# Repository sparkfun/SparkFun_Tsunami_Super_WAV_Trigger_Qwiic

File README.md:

SparkFun Tsunami Super WAV Trigger (Qwiic)
========================================

<table class="table table-hover table-striped table-bordered">
  <tr align="center">
   <td></td>
   <td></td>
  </tr>
  <tr align="center">
   <td><i>SparkFun Tsunami Super WAV Trigger (Qwiic)<br /> - 32 Voices <br />[ <a href="https://www.sparkfun.com/products/18159">WIG-18159</a> ]</i></td>
   <td><i>SparkFun Tsunami Super WAV Trigger (Qwiic)<br /> - 25 Voices <br />[ <a href="https://www.sparkfun.com/products/20636">WIG-20636</a> ]</i></td>
  </tr>
</table>

Tsunami is a polyphonic Wav file player with 4 stereo (or 8 mono) outputs.  Wav files can be triggered using the 16 onboard contacts, via MIDI, serial connection or Qwiic to a PC or other microcontroller.

Repository Contents
-------------------

* **/Documentation** - Data sheets, additional product information
* **/Hardware** - Eagle design files (.brd, .sch)
* **/Production** - Production panel files (.brd)
* **/Example_WAV_files/MONO** - example WAV Files for use with _mono_ firmware and the [Qwiic Arduino Library Examples](https://github.com/sparkfun/SparkFun_Tsunami_Qwiic_Arduino_Library).
* **/Example_WAV_files/STEREO** - example WAV Files for use with _stereo_ firmware

Documentation
--------------
* **[Hookup Guide](https://learn.sparkfun.com/tutorials/tsunami-super-wav-trigger-hookup-guide)** - Basic hookup guide for Tsunami Qwiic.
* **[Official User Guide](https://cdn.sparkfun.com/assets/e/9/9/8/e/Tsunami_UserGuide_20230114.pdf)** - More detailed user guide, written by Robertsonics.
* **[Official Downloads Page](http://robertsonics.com/downloads/)** - Download supporting files, including firmware updates and the configuration utility.
* **[SparkFun Tsunami Qwiic Arduino Library](https://github.com/sparkfun/SparkFun_Tsunami_Qwiic_Arduino_Library)** - Arduino Library for I2C control via Qwiic cable.
* **[Tsunami Arduino Serial Library](https://github.com/robertsonics/Tsunami-Arduino-Serial-Library)** - Arduino Library for Serial interface control via RX/TX.
* **[SparkFun Fritzing repo](https://github.com/sparkfun/Fritzing_Parts/blob/main/products/13810_Tsunami_Super_WAV_Trigger.fzpz)** - Fritzing diagrams for SparkFun products.
* **[SparkFun 3D Model repo](https://github.com/sparkfun/3D_Models)** - 3D models of SparkFun products.

Product Versions
----------------
* [WIG-20636](https://www.sparkfun.com/products/20636) - v21 with ATSAMS70N19, 25 Voices, and Qwiic supported! 
* [WIG-18159](https://www.sparkfun.com/products/18159) - v21 with ATSAMS70N20, 32 Voices, and Qwiic supported! 
* [WIG-13810](https://www.sparkfun.com/products/13810) - v11 First hardware revision (non-qwiic)

Version History
---------------
* [v21 Production Release](https://github.com/sparkfun/SparkFun_Tsunami_Super_WAV_Trigger_Qwiic/commit/4bed2473d8b69c6fbc46fcfe248d6b1637192635) - V21 hardware revision. There are different versions of this board that use the same PCB. To distinguish the two, check out the IC: ATSAMS70N20 for 32 voices and ATSAMS70N19 for 25 voices.
* [v11 Initial production Release](https://github.com/sparkfun/tsunami/commit/f42b14d72773535e83374cde73f2ca3f25164abb) - V11 hardware revision.

License Information
-------------------

The hardware design of Tsunami is _**open source**_!

Please review the LICENSE.md file for license information.

If you have any questions or concerns on licensing, please contact techsupport@sparkfun.com.

Distributed as-is; no warranty is given.

- Your friends at SparkFun.

Authors
----

Jamie Robertson @ Robertsonics, 
Pete Lewis @ SparkFun Electronics, 
Byron Jacquot @ SparkFun Electronics

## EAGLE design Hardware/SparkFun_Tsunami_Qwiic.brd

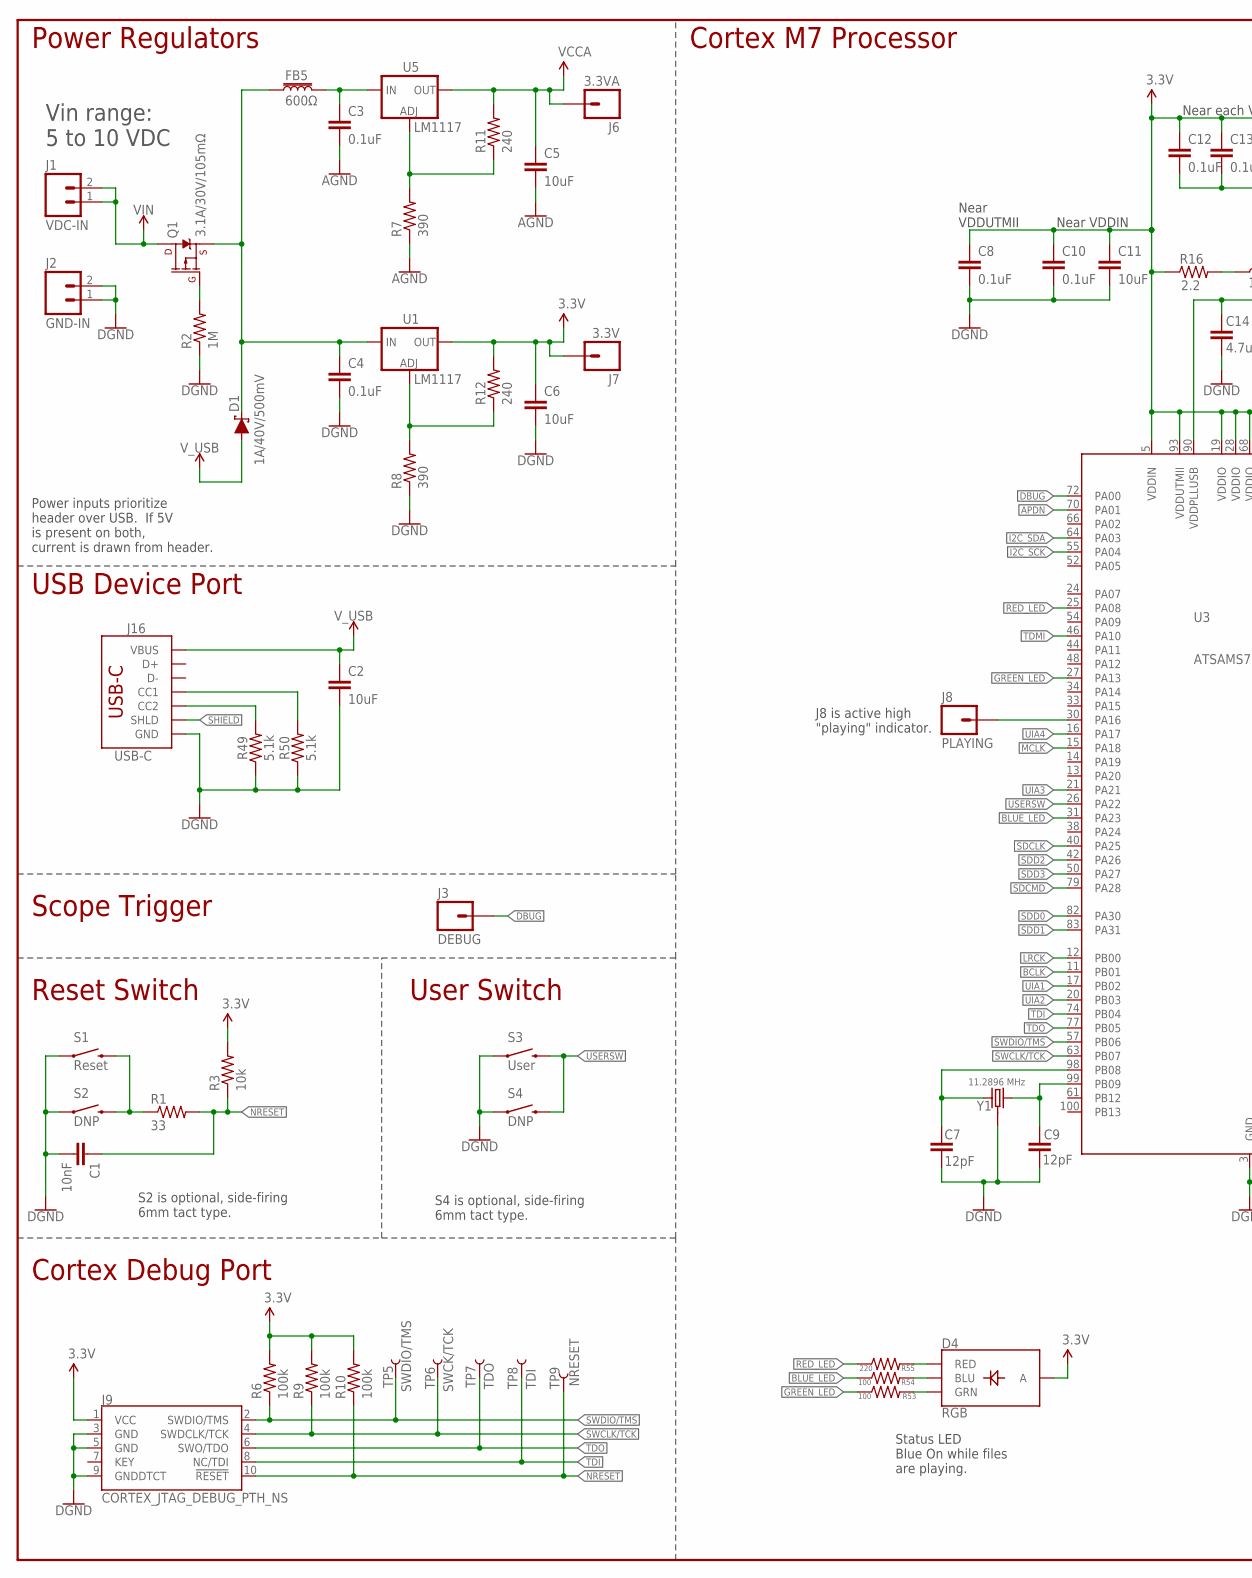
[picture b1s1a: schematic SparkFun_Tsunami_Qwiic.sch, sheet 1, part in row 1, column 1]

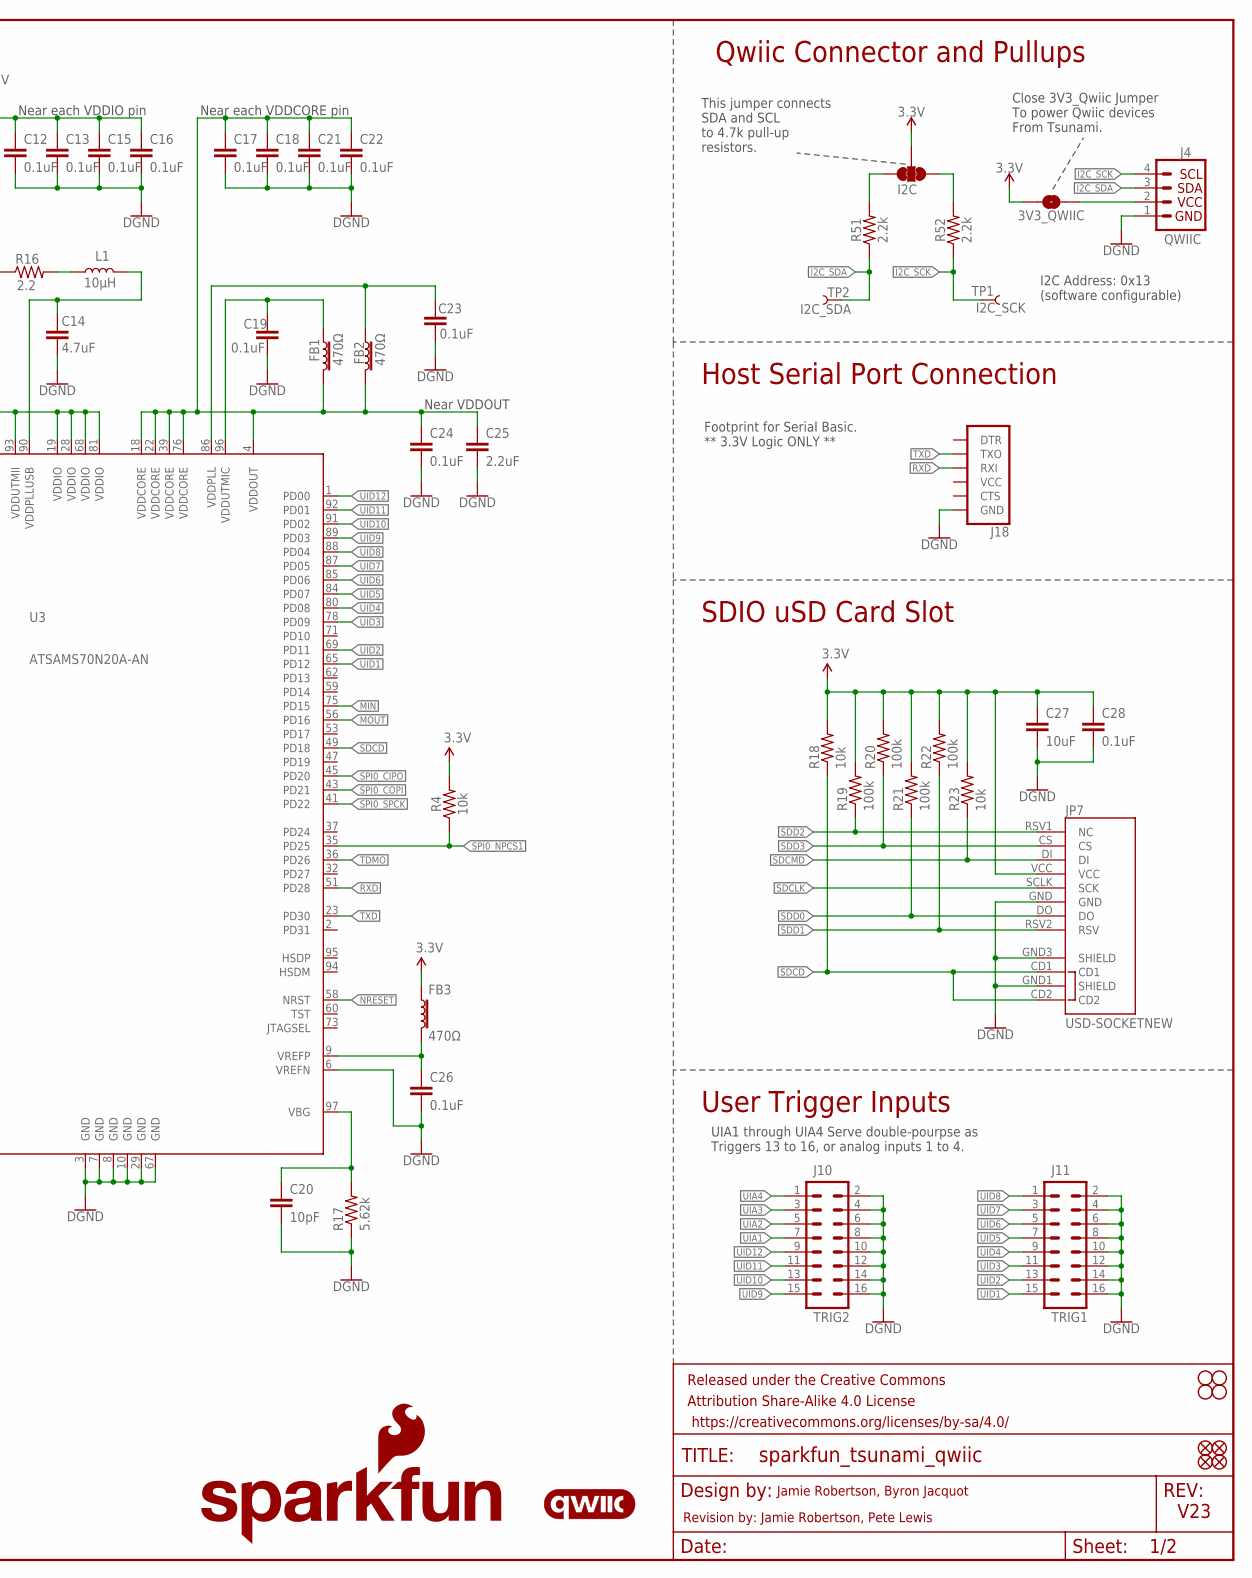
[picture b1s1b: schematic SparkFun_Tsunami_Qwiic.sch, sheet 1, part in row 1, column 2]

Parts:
3V3_QWIIC: JUMPER-SMT_2_NO_SILK; SMT-JUMPER_2_NO_SILK
C1: 10nF; 0402-TIGHT
C2, C5, C6, C11, C27: 10uF; 0402-TIGHT
C3, C4, C8, C10, C12, C13, C15, C16, C17, C18, C19, C21, C22, C23, C24, C26, C28: 0.1uF; 0402-TIGHT
C7, C9: 12pF; 0402-TIGHT
C14: 4.7uF; 0402-TIGHT
C20: 10pF; 0603
C25: 2.2uF; 0603
D1: 1A/40V/500mV; SMA-DIODE
D4: RGB; P-LCC-4-3
FB1, FB2, FB3: 470Ω; 0603
FB5: 600Ω; 0805
FD1, FD2, FD3, FD4: FIDUCIALUFIDUCIAL; FIDUCIAL-MICRO
FRAME1: FRAME-LEDGER; CREATIVE_COMMONS
H1, H2, H3, H4: STAND-OFF
I2C: JUMPER-SMT_3_2-NC_TRACE_SILK; SMT-JUMPER_3_2-NC_TRACE_SILK
J1: VDC-IN; 1X02_NO_SILK
J2: GND-IN; 1X02_NO_SILK
J3: DEBUG; 1X01_NO_SILK
J4: QWIIC; JST04_1MM_RA
J6: 3.3VA; 1X01_NO_SILK
J7: 3.3V; 1X01_NO_SILK
J8: PLAYING; 1X01_NO_SILK
J9: CORTEX_JTAG_DEBUG_PTH_NS; 2X5-PTH-1.27MM-NO_SILK
J10: TRIG2; 2X8_NOSILK
J11: TRIG1; 2X8_NOSILK
J16: USB-C; USB-C-16P-4LAYER-ISOLATED
J18: 6_PIN_SERIAL_TARGETSILK; 6_PIN_SERIAL_TARGET_SIDE_W_SILK
JP7: USD-SOCKETNEW; MICRO-SD-SOCKET-PP
L1: 10μH; 0805
LOGO2: SFE_LOGO_NAME_FLAME.2_INCH; SFE_LOGO_NAME_FLAME_.2
LOGO3: QWIIC_LOGO_4MM; QWIIC_4MM
Q1: 3.1A/30V/105mΩ; SOT23-3
R1: 33; 0603
R2: 1M; 0603
R3, R4, R18, R23: 10k; 0402-TIGHT
R6, R9, R10, R19, R20, R21, R22: 100k; 0402-TIGHT
R7, R8: 390; 0603
R11, R12: 240; 0603
R16: 2.2; 0603
R17: 5.62k; 0603
R49, R50: 5.1k; 0402-TIGHT
R51, R52: 2.2k; 0402-TIGHT
R53, R54: 100; 0603
R55: 220; 0603
S1: Reset; TACTILE_SWITCH_SMD_5.2MM
S2, S4: DNP; TACTILE_SWITCH_PTH_RIGHT_ANGLE
S3: User; TACTILE_SWITCH_SMD_5.2MM
TP1: I2C_SCK; PAD.03X.05
TP2: I2C_SDA; PAD.03X.05
TP5: SWDIO/TMS; PAD.03X.05
TP6: SWCK/TCK; PAD.03X.05
TP7: TDO; PAD.03X.05
TP8: TDI; PAD.03X.05
TP9: NRESET; PAD.03X.05
U1, U5: LM1117; SOT223
U3: ATSAMS70N20A-AN; LQFP100
Y1: 11.2896 MHz; CRYSTAL-SMD-3.2X2.5MM_GEYER_12.60421

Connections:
3.3V: 3V3_QWIIC.1, C6.1, C8.1, C10.1, C11.1, C12.1, C13.1, C15.1, C16.1, C27.1, C28.1, D4.4 (A), FB3.1, I2C.2, J7.1, J9.1 (VCC), JP7.VCC, R3.2, R4.2, R6.2, R9.2, R10.2, R12.2, R16.1, R18.2, R19.2, R20.2, R21.2, R22.2, R23.2, U1.2 (OUT), U1.4 (OUT), U3.5 (VDDIN), U3.19 (VDDIO), U3.28 (VDDIO), U3.68 (VDDIO), U3.81 (VDDIO), U3.93 (VDDUTMII); also elsewhere on the board
AGND: C3.2, C5.2, R7.1; also elsewhere on the board
APDN: U3.70 (PA01); also elsewhere on the board
BCLK: U3.11 (PB01); also elsewhere on the board
BLUE_LED: R54.1, U3.31 (PA23)
CC1: J16.A5 (CC1), R50.2
CC2: J16.B5 (CC2), R49.2
DBUG: J3.1, U3.72 (PA00)
DGND: C1.2, C2.2, C4.2, C6.2, C7.2, C8.2, C9.2, C10.2, C11.2, C12.2, C13.2, C14.2, C15.2, C16.2, C17.2, C18.2, C19.2, C20.2, C21.2, C22.2, C23.2, C24.2, C25.2, C26.2, C27.2, C28.2, J2.1, J2.2, J4.1, J9.3 (GND), J9.5 (GND), J9.9 (GNDDTCT), J10.2, J10.4, J10.6, J10.8, J10.10, J10.12, J10.14, J10.16, J11.2, J11.4, J11.6, J11.8, J11.10, J11.12, J11.14, J11.16, J16.GND, J16.GND2 (GND), J18.6 (GND), JP7.GND, JP7.GND1 (SHIELD), JP7.GND3 (SHIELD), R2.1, R8.1, R17.1, R49.1, R50.1, S1.1, S2.1, S3.1, S4.1, U3.3 (GND), U3.6 (VREFN), U3.7 (GND), U3.8 (GND), U3.10 (GND), U3.29 (GND), U3.67 (GND), Y1.2 (3), Y1.4 (3); also elsewhere on the board
GREEN_LED: R53.1, U3.27 (PA13)
I2C_SCK: J4.4, R52.1, TP1.1, U3.55 (PA04)
I2C_SDA: J4.3, R51.1, TP2.1, U3.64 (PA03)
LRCK: U3.12 (PB00); also elsewhere on the board
MCLK: U3.15 (PA18); also elsewhere on the board
MIN: U3.75 (PD15); also elsewhere on the board
MOUT: U3.56 (PD16); also elsewhere on the board
unnamed: C7.1, U3.98 (PB08), Y1.1
unnamed: C9.1, U3.99 (PB09), Y1.3 (2)
unnamed: C19.1, FB1.1, U3.96 (VDDUTMIC)
unnamed: C14.1, L1.2, U3.90 (VDDPLLUSB)
unnamed: C23.1, FB2.1, U3.86 (VDDPLL)
unnamed: I2C.3, R51.2
unnamed: J8.1, U3.30 (PA16)
unnamed: I2C.1, R52.2
unnamed: C20.1, R17.2, U3.97 (VBG)
unnamed: C26.1, FB3.2, U3.9 (VREFP)
unnamed: L1.1, R16.2
unnamed: R7.2, R11.1, U5.1 (ADJ)
unnamed: R1.1, S1.3 (2), S2.2
unnamed: R8.2, R12.1, U1.1 (ADJ)
unnamed: 3V3_QWIIC.2, J4.2
unnamed: D4.2 (GRN), R53.2
unnamed: D4.3 (BLU), R54.2
unnamed: D4.1 (RED), R55.2
unnamed: C3.1, FB5.2, U5.3 (IN)
unnamed: Q1.1 (G), R2.2
NRESET: C1.1, J9.10 (!RESET), R1.2, R3.1, R10.1, TP9.1, U3.58 (NRST)
RED_LED: R55.1, U3.25 (PA08)
REGINPUTS: C4.1, D1.C, FB5.1, Q1.2 (S), U1.3 (IN)
RXD: J18.3 (RXI), U3.51 (PD28)
SDCD: JP7.CD1, JP7.CD2, R18.1, U3.49 (PD18)
SDCLK: JP7.SCLK (SCK), U3.40 (PA25)
SDCMD: JP7.DI, R23.1, U3.79 (PA28)
SDD0: JP7.DO, R21.1, U3.82 (PA30)
SDD1: JP7.RSV2 (RSV), R22.1, U3.83 (PA31)
SDD2: JP7.RSV1 (NC), R19.1, U3.42 (PA26)
SDD3: JP7.CS, R20.1, U3.50 (PA27)
SHIELD: J16.SHLD1 (SHLD), J16.SHLD2 (SHLD), J16.SHLD3 (SHLD), J16.SHLD4 (SHLD), J16.SHLD5 (SHLD), J16.SHLD6 (SHLD), J16.SHLD7 (SHLD), J16.SHLD8 (SHLD)
SPI0_CIPO: U3.45 (PD20); also elsewhere on the board
SPI0_COPI: U3.43 (PD21); also elsewhere on the board
SPI0_NPCS1: R4.1, U3.35 (PD25); also elsewhere on the board
SPI0_SPCK: U3.41 (PD22); also elsewhere on the board
SWCLK/TCK: J9.4 (SWDCLK/TCK), R9.1, TP6.1, U3.63 (PB07)
SWDIO/TMS: J9.2 (SWDIO/TMS), R6.1, TP5.1, U3.57 (PB06)
TDI: J9.8 (NC/TDI), TP8.1, U3.74 (PB04)
TDMI: U3.46 (PA10); also elsewhere on the board
TDMO: U3.36 (PD26); also elsewhere on the board
TDO: J9.6 (SWO/TDO), TP7.1, U3.77 (PB05)
TXD: J18.2 (TXO), U3.23 (PD30)
UIA1: J10.7, U3.17 (PB02)
UIA2: J10.5, U3.20 (PB03)
UIA3: J10.3, U3.21 (PA21)
UIA4: J10.1, U3.16 (PA17)
UID1: J11.15, U3.65 (PD12)
UID2: J11.13, U3.69 (PD11)
UID3: J11.11, U3.78 (PD09)
UID4: J11.9, U3.80 (PD08)
UID5: J11.7, U3.84 (PD07)
UID6: J11.5, U3.85 (PD06)
UID7: J11.3, U3.87 (PD05)
UID8: J11.1, U3.88 (PD04)
UID9: J10.15, U3.89 (PD03)
UID10: J10.13, U3.91 (PD02)
UID11: J10.11, U3.92 (PD01)
UID12: J10.9, U3.1 (PD00)
USERSW: S3.3 (2), S4.2, U3.26 (PA22)
VCCA: C5.1, J6.1, R11.2, U5.2 (OUT), U5.4 (OUT); also elsewhere on the board
VDDOUT: C17.1, C18.1, C21.1, C22.1, C24.1, C25.1, FB1.2, FB2.2, U3.4 (VDDOUT), U3.18 (VDDCORE), U3.22 (VDDCORE), U3.39 (VDDCORE), U3.76 (VDDCORE)
VIN: J1.1, J1.2, Q1.3 (D)
V_USB: C2.1, D1.A, J16.VBUS1 (VBUS), J16.VBUS2 (VBUS)

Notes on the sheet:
Jamie Robertson, Byron Jacquot
V23
Near each VDDCORE pin
Near each VDDIO pin
Near VDDUTMII
Near VDDIN
Near VDDOUT
Power Regulators
USB Device Port
Scope Trigger
Cortex Debug Port
Cortex M7 Processor
SDIO uSD Card Slot
User Trigger Inputs
Reset Switch
S2 is optional, side-firing 6mm tact type.
Vin range: 5 to 10 VDC
Status LED Blue On while files are playing.
Power inputs prioritize header over USB. If 5V is present on both, current is drawn from header.
UIA1 through UIA4 Serve double-pourpse as Triggers 13 to 16, or analog inputs 1 to 4.
Host Serial Port Connection
Footprint for Serial Basic. ** 3.3V Logic ONLY **
User Switch
J8 is active high "playing" indicator.
S4 is optional, side-firing 6mm tact type.
This jumper connects SDA and SCL to 4.7k pull-up resistors.
Revision by: Jamie Robertson, Pete Lewis
Qwiic Connector and Pullups
Close 3V3_Qwiic Jumper To power Qwiic devices From Tsunami.
I2C Address: 0x13 (software configurable)

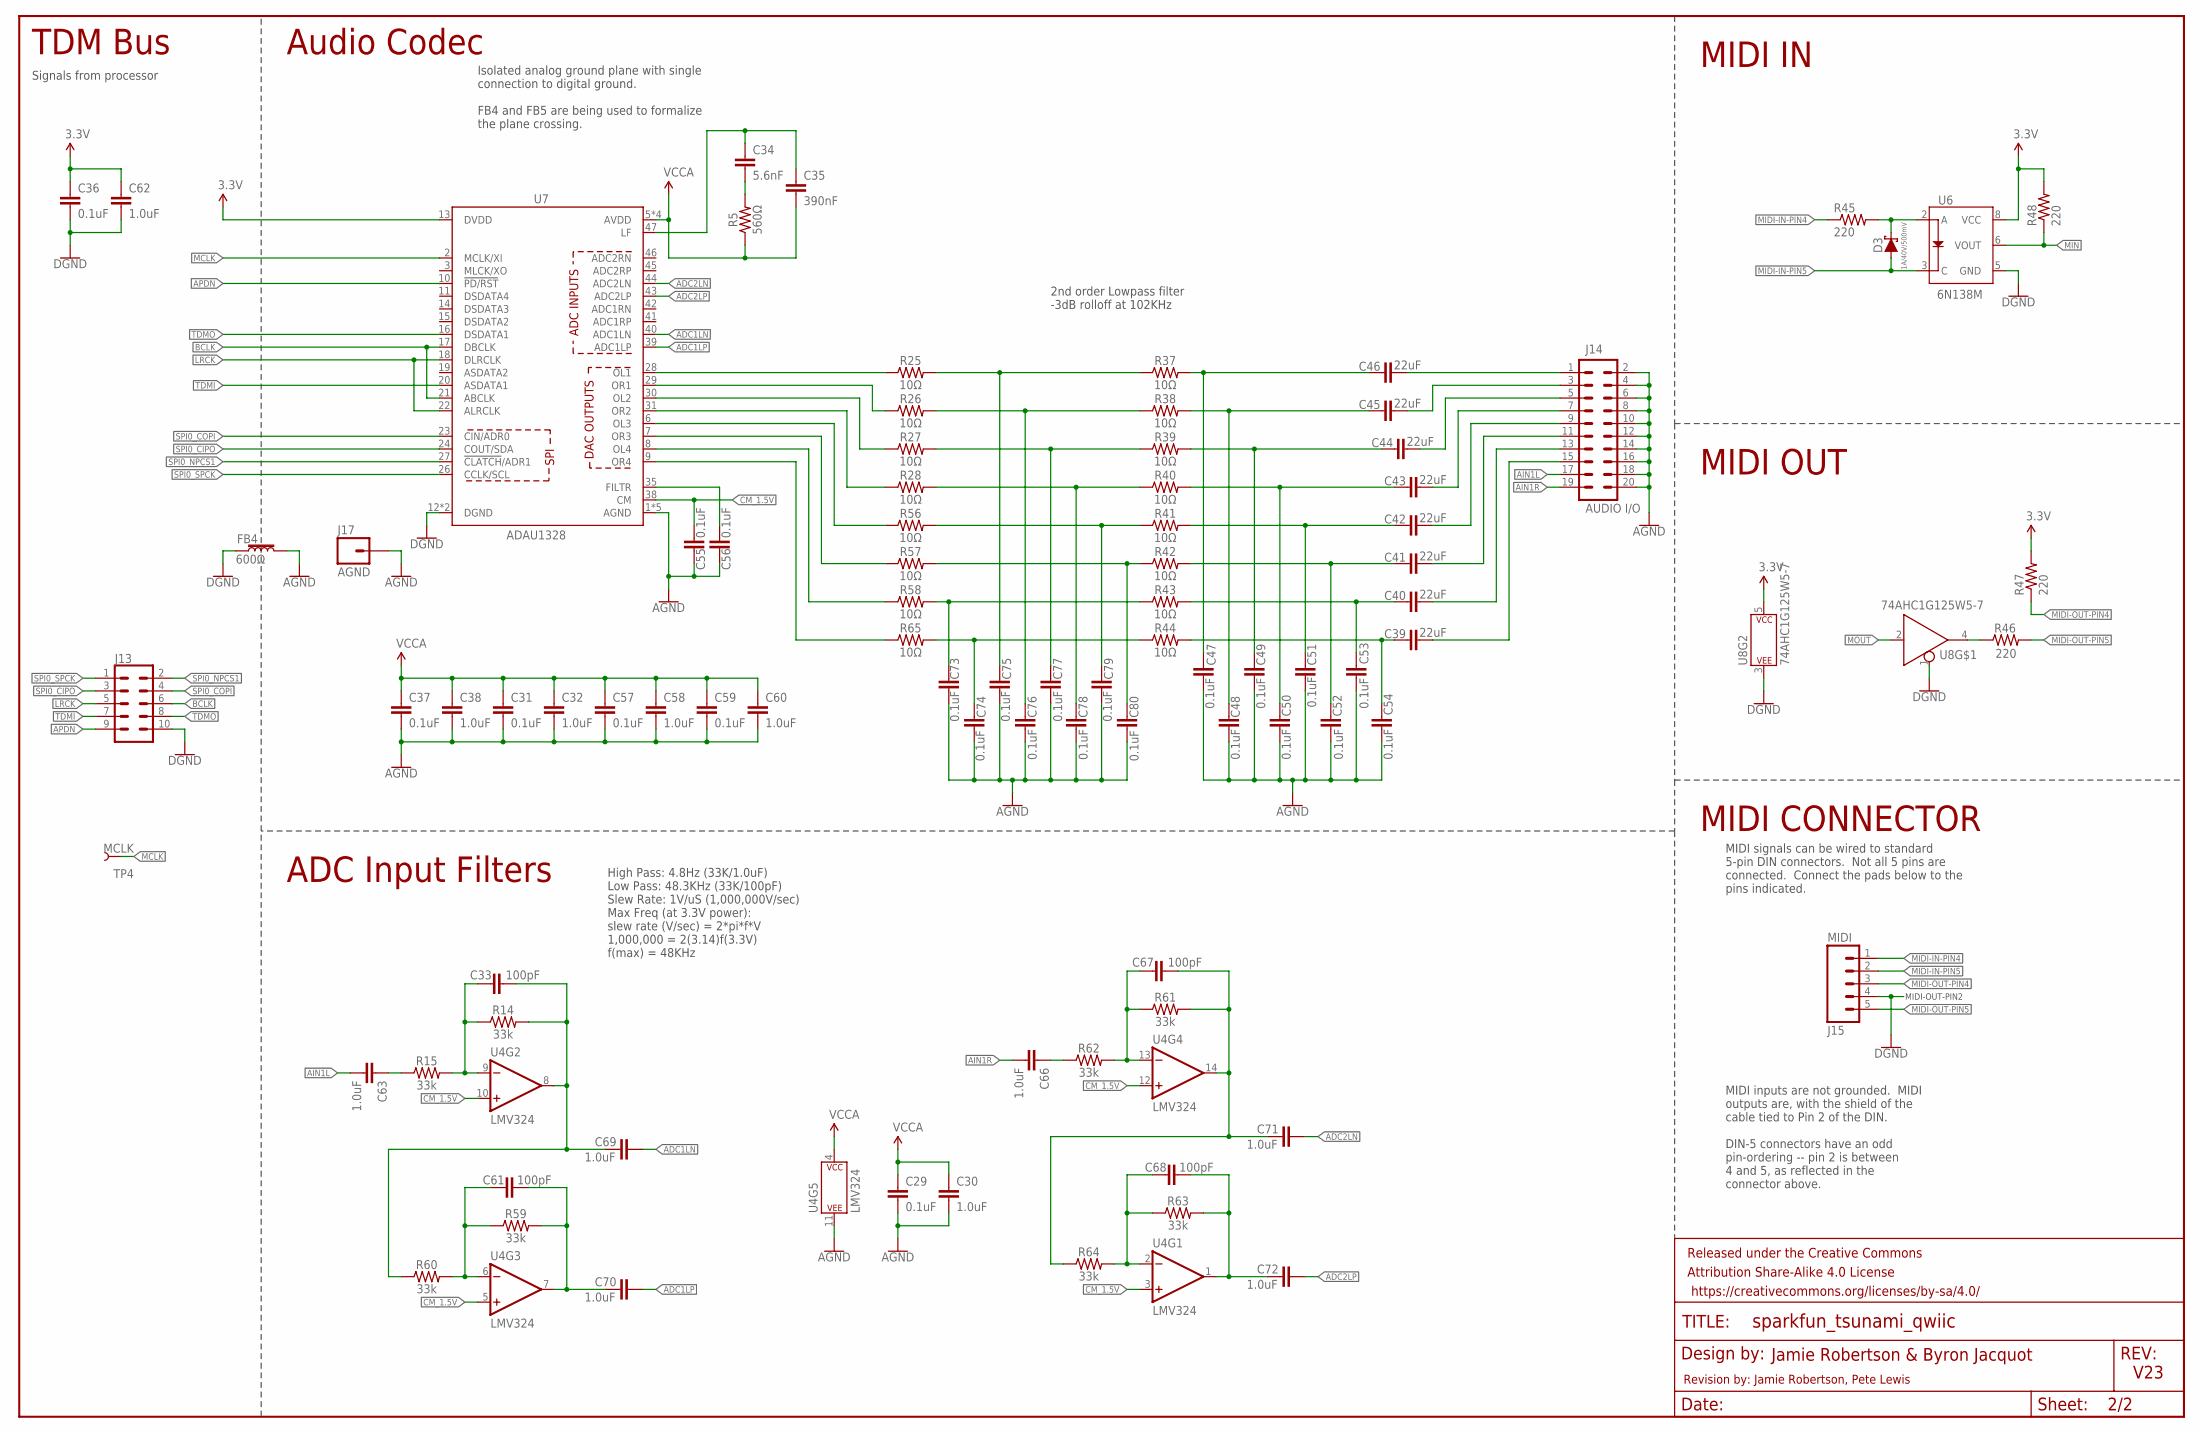
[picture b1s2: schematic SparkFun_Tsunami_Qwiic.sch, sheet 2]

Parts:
C29, C31, C36, C37, C47, C48, C49, C50, C51, C52, C53, C54, C55, C56, C57, C59, C73, C74, C75, C76, C77, C78, C79, C80: 0.1uF; 0402-TIGHT
C30, C32, C38, C58, C60, C62, C63, C66, C69, C70, C71, C72: 1.0uF; 0402-TIGHT
C33, C61, C67, C68: 100pF; 0402-TIGHT
C34: 5.6nF; 0603
C35: 390nF; 0603
C39, C40, C41, C42, C43, C44, C45, C46: 22uF; 0805
D3: 1A/40V/500mV; SMA-DIODE
FB4: 600Ω; 0805
FRAME2: FRAME-LEDGER; CREATIVE_COMMONS
J13: CONN_05X2NO_SILK; 2X5_NOSILK
J14: AUDIO I/O; 2X10_NOSILK
J15: MIDI; 1X05_NO_SILK
J17: AGND; 1X01_NO_SILK
R5: 560Ω; 0402-TIGHT
R14, R15, R59, R60, R61, R62, R63, R64: 33k; 0402-TIGHT
R25, R26, R27, R28, R37, R38, R39, R40, R41, R42, R43, R44, R56, R57, R58, R65: 10Ω; 0402-TIGHT
R45, R46, R47, R48: 220; 0603
TP4: MCLK; PAD.03X.05
U4: LMV324; SO14
U6: 6N138M; 8-SMD
U7: ADAU1328; LQFP-48
U8: 74AHC1G125W5-7; SOT23-5

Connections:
3.3V: C36.1, C62.1, R47.2, R48.2, U6.8 (VCC), U7.13 (DVDD), U8.5 (P$V+); also elsewhere on the board
56: D3.C, R45.2, U6.2 (A)
ADC1LN: C69.1, U7.40 (ADC1LN)
ADC1LP: C70.1, U7.39 (ADC1LP)
ADC2LN: C71.1, U7.44 (ADC2LN)
ADC2LP: C72.1, U7.43 (ADC2LP)
AGND: C29.2, C30.2, C31.2, C32.2, C37.2, C38.2, C47.2, C48.2, C49.2, C50.2, C51.2, C52.2, C53.2, C54.2, C55.2, C56.2, C57.2, C58.2, C59.2, C60.2, C73.1, C74.1, C75.1, C76.1, C77.1, C78.1, C79.1, C80.1, FB4.2, J14.2, J14.4, J14.6, J14.8, J14.10, J14.12, J14.14, J14.16, J14.18, J14.20, J17.1, U4.11 (P$V-), U7.1 (AGND), U7.4 (AGND), U7.32 (AGND), U7.34 (AGND), U7.36 (AGND); also elsewhere on the board
AIN1L: C63.2, J14.17
AIN1R: C66.2, J14.19
AOUT1L: C46.1, C47.1, R37.2
AOUT1R: C45.1, C48.1, R38.2
AOUT2L: C44.2, J14.5
AOUT2R: C43.1, C50.1, R40.2
AOUT3L: C42.2, J14.9
AOUT3R: C41.1, C52.1, R42.2
AOUT4L: C40.1, C53.1, R43.2
AOUT4R: C39.1, C54.1, R44.2
APDN: J13.9, U7.10 (!PD/RST!); also elsewhere on the board
BCLK: J13.6, U7.17 (DBCLK), U7.21 (ABCLK); also elsewhere on the board
CM_1.5V: C55.1, U4.3 (+IN), U4.5 (+IN), U4.10 (+IN), U4.12 (+IN), U7.38 (CM)
DGND: C36.2, C62.2, FB4.1, J13.10, J15.4, U6.5 (GND), U7.12 (DGND), U7.25 (DGND), U8.1 (!EN), U8.3 (P$V-); also elsewhere on the board
LF: C34.1, C35.1, U7.47 (LF)
LRCK: J13.5, U7.18 (DLRCLK), U7.22 (ALRCLK); also elsewhere on the board
MCLK: TP4.1, U7.2 (MCLK/XI); also elsewhere on the board
MIDI-IN-PIN4: J15.1, R45.1
MIDI-IN-PIN5: D3.A, J15.2, U6.3 (C)
MIDI-OUT-PIN4: J15.3, R47.1
MIDI-OUT-PIN5: J15.5, R46.2
MIN: R48.1, U6.6 (VOUT); also elsewhere on the board
MOUT: U8.2 (A); also elsewhere on the board
unnamed: C33.2, C69.2, R14.2, R60.1, U4.8 (OUT)
unnamed: C34.2, R5.2
unnamed: C63.1, R15.1
unnamed: C61.2, C70.2, R59.2, U4.7 (OUT)
unnamed: C68.2, C72.2, R63.2, U4.1 (OUT)
unnamed: C39.2, J14.15
unnamed: C40.2, J14.13
unnamed: C41.2, J14.11
unnamed: C42.1, C51.1, R41.2
unnamed: C43.2, J14.7
unnamed: C75.2, R25.2, R37.1
unnamed: C74.2, R44.1, R65.2
unnamed: C73.2, R43.1, R58.2
unnamed: C80.2, R42.1, R57.2
unnamed: C44.1, C49.1, R39.2
unnamed: C46.2, J14.1
unnamed: C45.2, J14.3
unnamed: R46.1, U8.4 (Y)
unnamed: C56.1, U7.35 (FILTR)
unnamed: C61.1, R59.1, R60.2, U4.6 (-IN)
unnamed: C33.1, R14.1, R15.2, U4.9 (-IN)
unnamed: C79.2, R41.1, R56.2
unnamed: C78.2, R28.2, R40.1
unnamed: C76.2, R26.2, R38.1
unnamed: C77.2, R27.2, R39.1
unnamed: C67.2, C71.2, R61.2, R64.1, U4.14 (OUT)
unnamed: C66.1, R62.1
unnamed: C68.1, R63.1, R64.2, U4.2 (-IN)
unnamed: C67.1, R61.1, R62.2, U4.13 (-IN)
OL1: R25.1, U7.28 (OL1)
OL2: R27.1, U7.30 (OL2)
OL3: R56.1, U7.6 (OL3)
OL4: R58.1, U7.8 (OL4)
OR1: R26.1, U7.29 (OR1)
OR2: R28.1, U7.31 (OR2)
OR3: R57.1, U7.7 (OR3)
OR4: R65.1, U7.9 (OR4)
SPI0_CIPO: J13.3, U7.24 (COUT/SDA); also elsewhere on the board
SPI0_COPI: J13.4, U7.23 (CIN/ADR0); also elsewhere on the board
SPI0_NPCS1: J13.2, U7.27 (!CLATCH!/ADR1); also elsewhere on the board
SPI0_SPCK: J13.1, U7.26 (CCLK/SCL); also elsewhere on the board
TDMI: J13.7, U7.20 (ASDATA1); also elsewhere on the board
TDMO: J13.8, U7.16 (DSDATA1); also elsewhere on the board
VCCA: C29.1, C30.1, C31.1, C32.1, C35.2, C37.1, C38.1, C57.1, C58.1, C59.1, C60.1, R5.1, U4.4 (P$V+), U7.5 (AVDD), U7.33 (AVDD), U7.37 (AVDD), U7.48 (AVDD); also elsewhere on the board

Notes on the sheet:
Isolated analog ground plane with single connection to digital ground. FB4 and FB5 are being used to formalize the plane crossing.
Audio Codec
MIDI IN
MIDI OUT
Jamie Robertson & Byron Jacquot
V23
TDM Bus
Signals from processor
MIDI CONNECTOR
MIDI signals can be wired to standard 5-pin DIN connectors. Not all 5 pins are connected. Connect the pads below to the pins indicated.
MIDI-OUT-PIN2
MIDI inputs are not grounded. MIDI outputs are, with the shield of the cable tied to Pin 2 of the DIN. DIN-5 connectors have an odd pin-ordering -- pin 2 is between 4 and 5, as reflected in the connector above.
2nd order Lowpass filter -3dB rolloff at 102KHz
ADC Input Filters
High Pass: 4.8Hz (33K/1.0uF) Low Pass: 48.3KHz (33K/100pF) Slew Rate: 1V/uS (1,000,000V/sec) Max Freq (at 3.3V power): slew rate (V/sec) = 2*pi*f*V 1,000,000 = 2(3.14)f(3.3V) f(max) = 48KHz
Revision by: Jamie Robertson, Pete Lewis

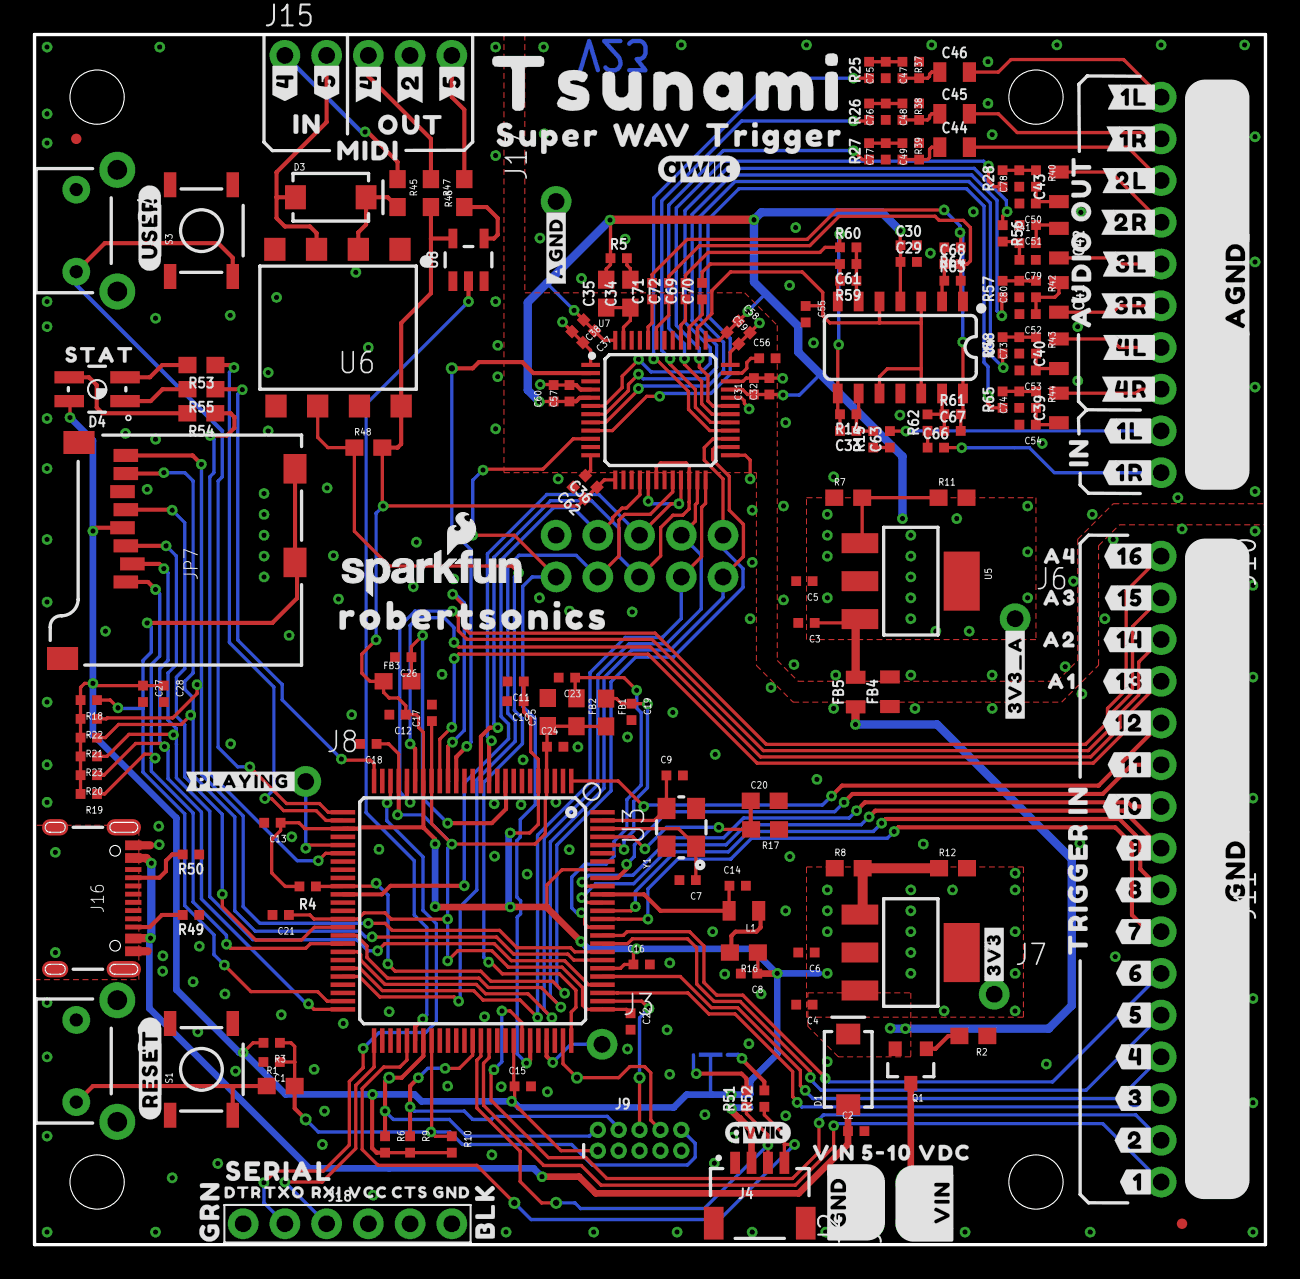
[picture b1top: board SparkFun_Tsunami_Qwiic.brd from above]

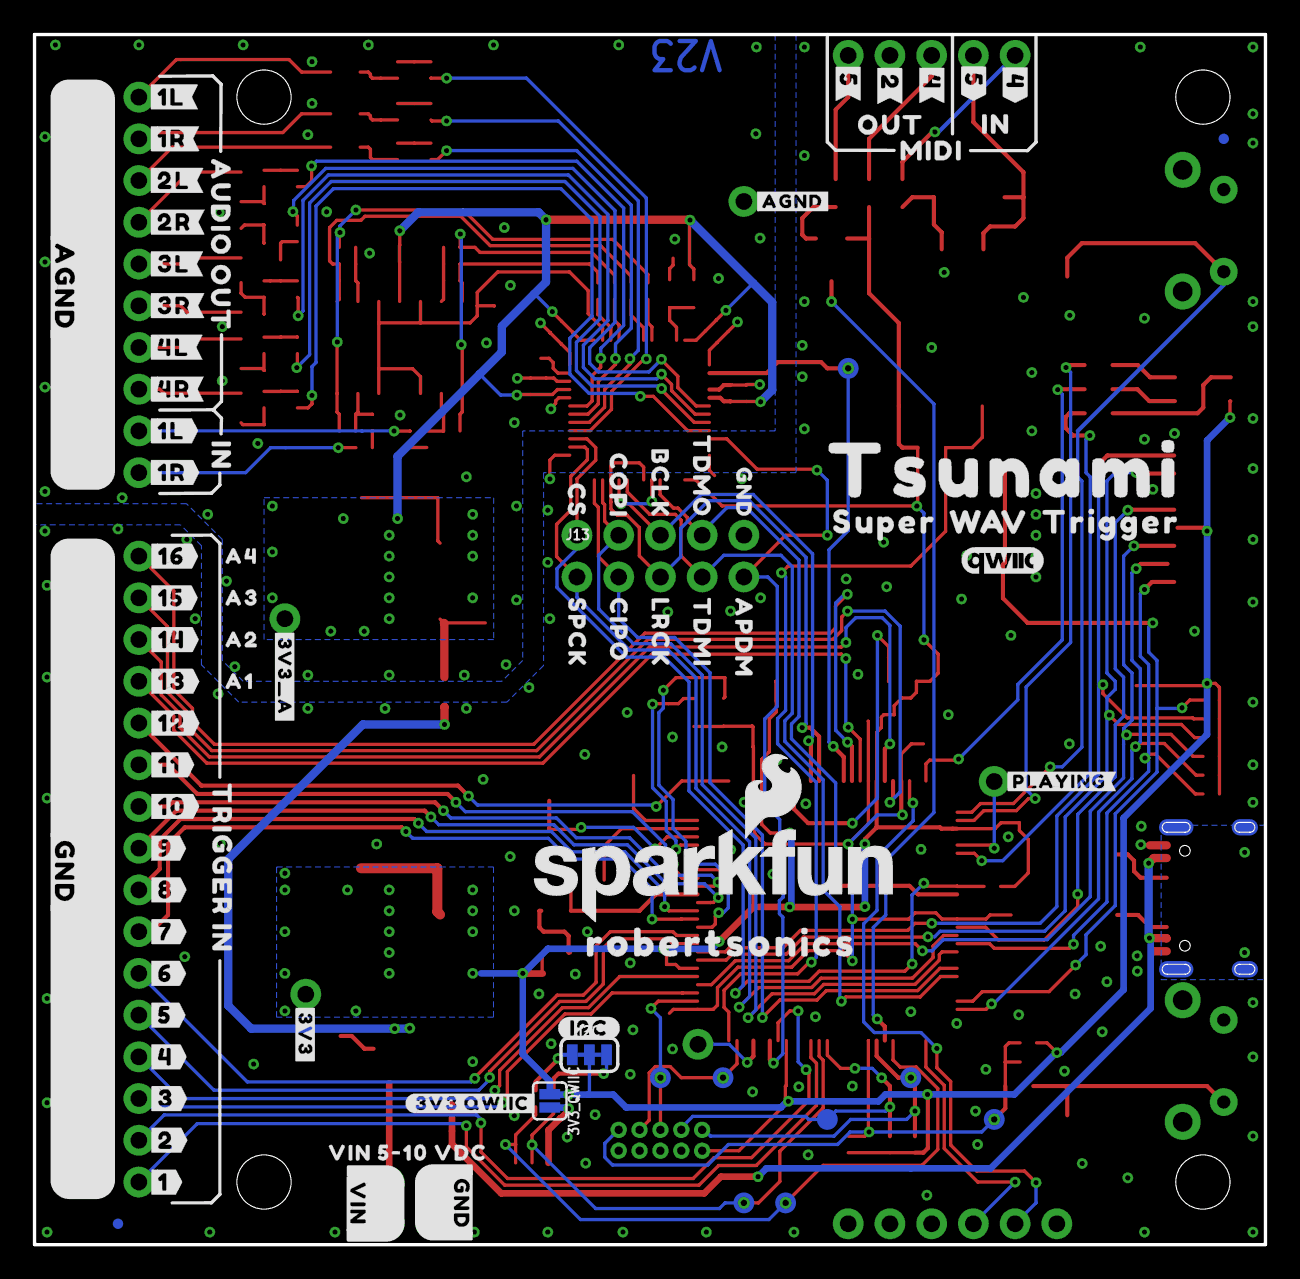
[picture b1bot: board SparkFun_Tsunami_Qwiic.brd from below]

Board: 2 copper layers, 74.9 x 73.7 mm, 327 parts (84 on the bottom side), 138 nets.

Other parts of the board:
U$3: GND_0
U$4, U$73: QWIIC_5MM
U$5: STAT0
U$6: #USER#0
U$7: #RESET#0
U$8, U$9: ROBERTSONICS0
U$10, U$167: #2L#0
U$11: #1L#0
U$12, U$120: #1R#0
U$13: #2R#0
U$14: #3R#0
U$15: #3L#0
U$16: #4L#0
U$17: #4R#0
U$18: #4#3
U$19: #2#5
U$20, U$107: AUDIO_OUT0
U$21, U$46, U$108, U$123: IN0
U$22, U$106: TRIGGER_IN0
U$23, U$85: #GND#0
U$24: #1#0
U$25: SERIAL3
U$26, U$60: SUPER0
U$27, U$99: VIN_5#10_VDC0
U$28, U$84: #AGND#0
U$29: #2#0
U$30: #3#0
U$31, U$56, U$117: #4#0
U$32, U$58, U$118: #5#0
U$33: #6#0
U$34: #7#0
U$35: #8#0
U$36: #9#0
U$37: #10#0
U$38: #11#0
U$39: #12#0
U$40: #PLAYING#30
U$41, U$112: #3V3#0
U$43: #13#0
U$44: #3V3_A#0
U$45, U$122: MIDI0
U$47, U$124: OUT0
U$48: #14#0
U$49: #15#0
U$50: #16#0
U$51: A10
U$52: A20
U$53: A30
U$54: A40
U$55: #5#6
U$57: #2#6
U$59: #4#6
U$61, U$110: #GND#1
U$62, U$68: TRIGGER0
U$63, U$69: TSUNAMI0
U$64, U$70: W0
U$65, U$71: A0
U$66, U$72: V0
U$67, U$111: #VIN#2
U$74: #16#5
U$75: #15#17
U$76: #14#17
U$77: #13#17
U$78: #12#17
U$79: #11#17
U$80: #10#17
U$81: #9#17
U$82: #8#17
U$83: #7#17
U$86: CS17
U$87: BCLK19
U$88: COPI18
U$89: TDMO20
U$91: SPCK22
U$92: TDMI25
U$93: LRCK24
U$94: CIPO23
U$95: APDM26
U$96: #AGND#27
U$97: #AGND#28
U$98: #PLAYING#29
U$102: A117
U$103: A2118
U$104: A32119
U$105: A432120
U$113: #I2C#6
U$116: #1L#3
U$119: #1L#6
U$121: #1R#2
U$141: SFE_LOGO_NAME_FLAME_.1
U$162: #3V3_A#4
U$163: #3V3_QWIIC#0
U$164: #1R#3
U$165: #5#5
U$166: #1L#2
U$168: #2R#3
U$169: #3L#3
U$170: #3R#4
U$171: #4L#4
U$172: #4R#5
U$173: #6#17
U$174: #5#17
U$175: #4#17
U$176: #3#17
U$177: #2#17
U$178: #1#17

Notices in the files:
parts and their libraries:
SparkFun-Aesthetics: Licensing: Creative Commons ShareAlike 4.0 International - https://creativecommons.org/licenses/by-sa/4.0
SparkFun-Aesthetics: Released under the Creative Commons Attribution Share-Alike 4.0 License
SparkFun-Aesthetics: https://creativecommons.org/licenses/by-sa/4.0
